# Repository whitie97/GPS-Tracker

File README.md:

# GPS-Tracker
Low Power NB-IoT GPS Tracker

Battery or USB powered.

Block Diagram:

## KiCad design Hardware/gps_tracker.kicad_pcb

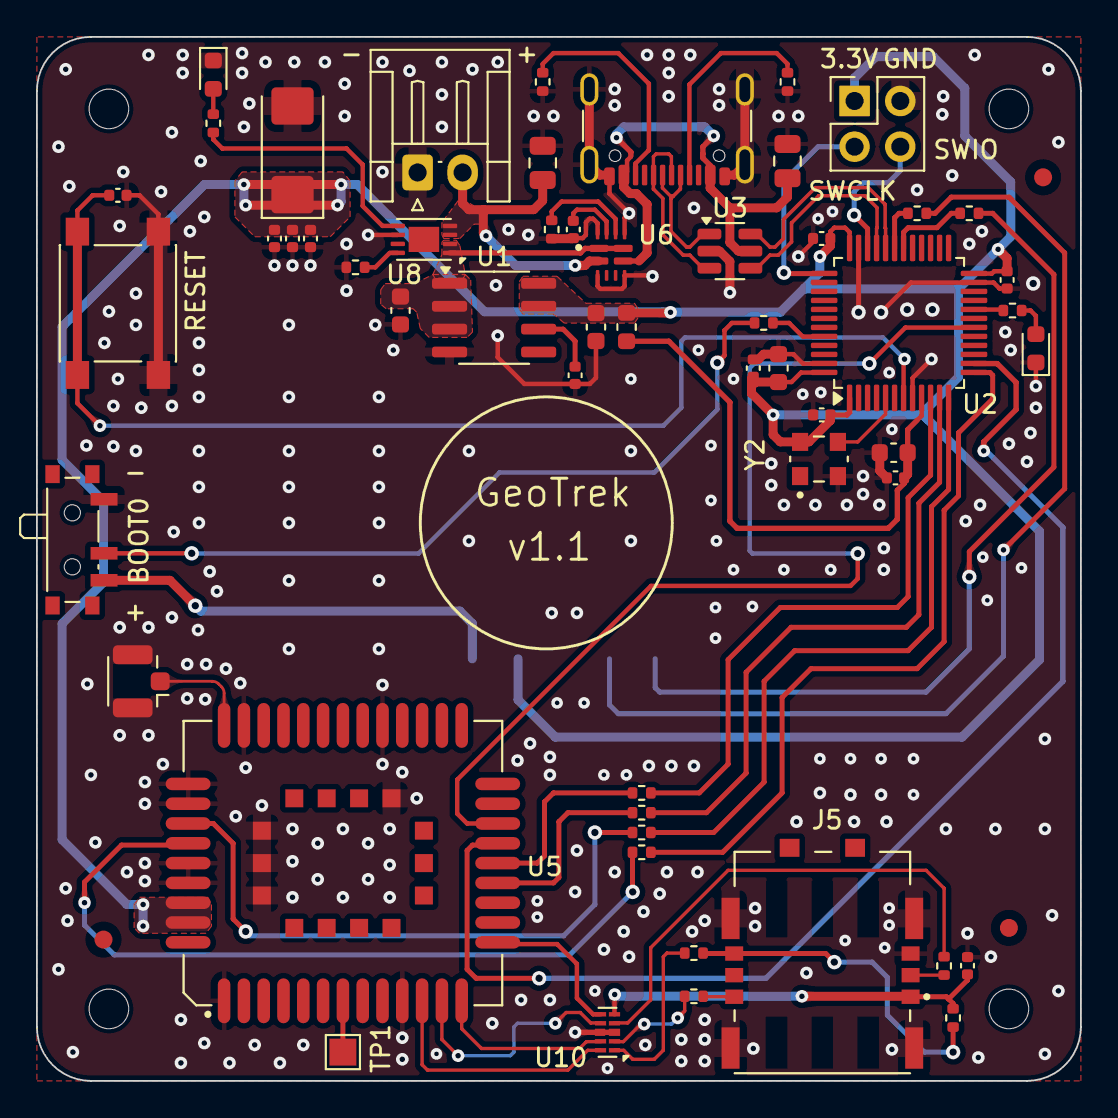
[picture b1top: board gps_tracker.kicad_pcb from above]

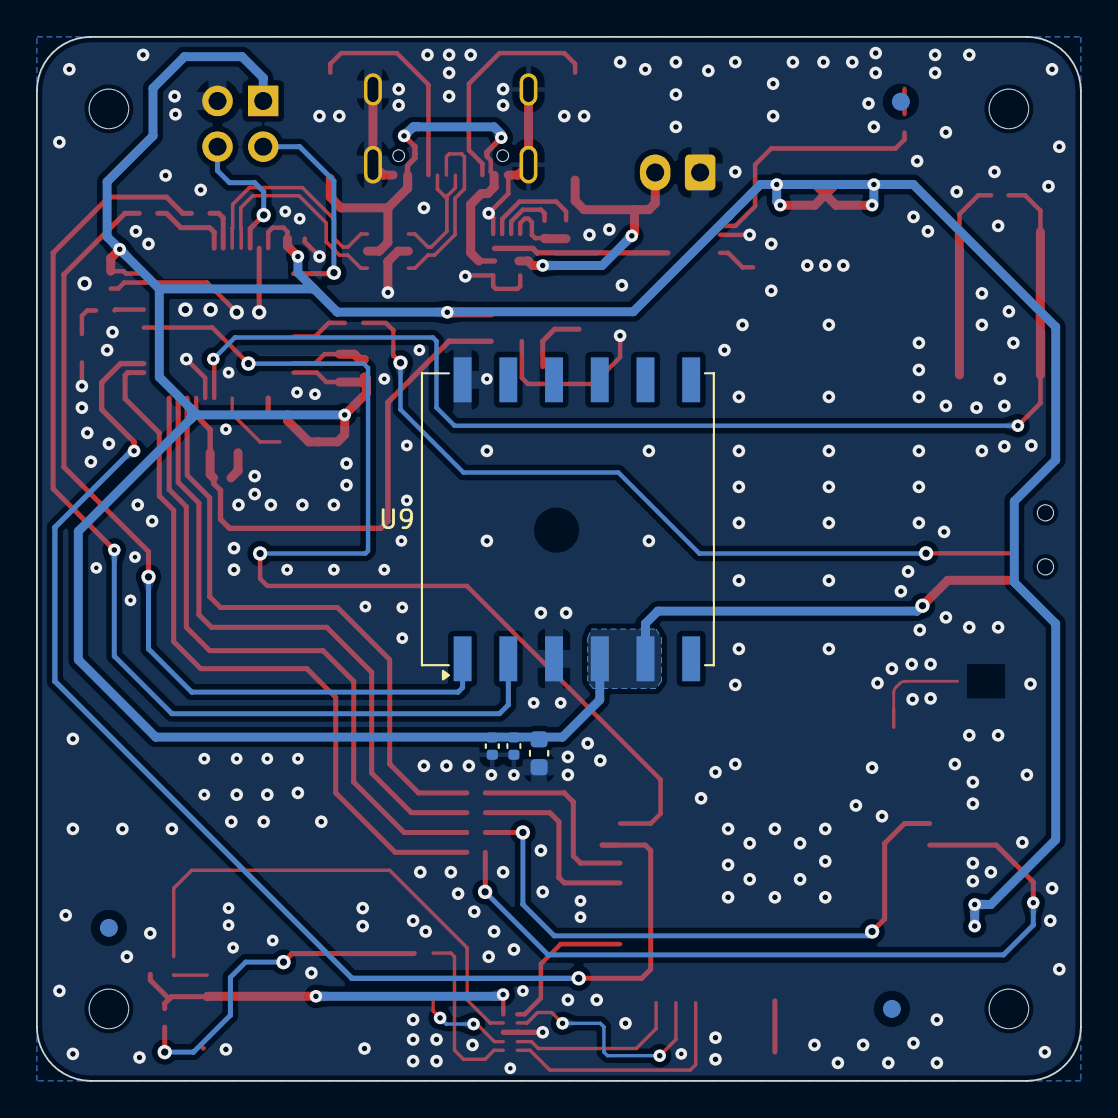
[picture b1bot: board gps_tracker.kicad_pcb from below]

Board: 4 copper layers, 58.0 x 58.0 mm, 69 parts (7 on the bottom side), 53 nets.

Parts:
C1, C2, C3, C4, C7, C8, C12, C13, C15, C21, C24, C25: 100nF; C_0402_1005Metric
C5, C6, C9, C10: 10uF; C_0603_1608Metric
C11: 1uF; C_0603_1608Metric
C14: 100uF; CP_EIA-6032-28_Kemet-C
C16: 100pF; C_0402_1005Metric
C17: 22pF; C_0402_1005Metric
C22, C23: 4.7uF; C_0805_2012Metric
D1, D2: LED; LED_0603_1608Metric
FB1: FerriteBead_Small; L_0603_1608Metric
FM1, FM2, FM3, FM4, FM5, FM6: Fiducial; Fiducial_1mm_Mask2mm
H1, H2, H3, H4: MountingHole_Pad; MountingHole_2.2mm_M2_ISO14580
J1: Conn_Coaxial; U.FL_Hirose_U.FL-R-SMT-1_Vertical
J2: Conn_01x02_Socket; JST_EH_S2B-EH_1x02_P2.50mm_Horizontal
J3: USB_C_Receptacle_USB2.0_16P; USB_C_Receptacle_GCT_USB4105-xx-A_16P_TopMnt_Horizontal
J4: Conn_02x02_Top_Bottom; PinHeader_2x02_P2.54mm_Vertical
J5: 104224-0820; MOLEX_104224-0820
R1, R2: 5.1K; R_0402_1005Metric
R3, R17: 10K; R_0402_1005Metric
R4, R14: 330R; R_0402_1005Metric
R5: 51.1K; R_0402_1005Metric
R6, R7, R15, R16: 1K; R_0402_1005Metric
R8, R9, R10, R11, R12: 22R; R_0402_1005Metric
R13: 2K; R_0402_1005Metric
SW1: SW_Push; SW_SPST_PTS645
SW2: SW_SPDT; SW_SPDT_PCM12
TP1: TestPoint; TestPoint_Pad_1.5x1.5mm
U1: MCP1727-3302xSN; SOIC-8_3.9x4.9mm_P1.27mm
U2: STM32L552CCTx; LQFP-48_7x7mm_P0.5mm
U3: USBLC6-2SC6; SOT-23-6
U5: BC660KGLAA-I03-SNASA; XCVR_BC660KGLAA-I03-SNASA
U6: TPS2121RUXR; IC_TPS2121RUXR
U8: MCP73831-2-MC; DFN-8-1EP_3x2mm_P0.5mm_EP1.7x1.4mm
U9: L80-R; Quectel_L80-R
U10: ESD224DQA; Diodes_UDFN-10_1.0x2.5mm_P0.5mm
Y2: ASEMB-24.000MHZ-LC-T; XTAL_ASEMB-24.000MHZ-LC-T

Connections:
+3.3V: C1.1, C2.1, C3.1, C4.1, C5.1, C6.1, C10.1, C14.1, C15.1, C16.1, C17.1, C24.1, C25.1, FB1.1, J4.1, SW2.3 (C), U1.7 (Sense), U1.8 (Vout), U2.1 (VBAT), U2.24 (VDD), U2.36 (VDD), U2.48 (VDD), U5.42 (VBAT), U5.43 (VBAT), U9.4 (VCC), U9.5 (V_BCKP), Y2.4 (VDD)
/CLK: R10.2, U10.2
/DATA: R8.2, U10.1
/ILIM: R5.1, U6.10 (ILIM)
/RST: R9.2, U10.4
/SS: C8.1, U6.11 (SS)
/SWD_CLK: J4.3, U2.37 (PA14)
/SWD_IO: J4.4, U2.34 (PA13)
/VCC: C21.1, J5.S1 (VCC), R17.1, U10.5
DBG_RXD_BC66: R15.1, U2.12 (PA2)
DBG_TXD_BC66: R16.1, U2.13 (PA3)
DN+: J3.A6 (D+), J3.B6 (D+), U3.3 (I/O2)
DN-: J3.A7 (D-), J3.B7 (D-), U3.1 (I/O1)
GND: C1.2, C2.2, C3.2, C4.2, C5.2, C6.2, C7.1, C8.2, C9.2, C10.2, C11.2, C12.2, C13.2, C14.2, C15.2, C16.2, C17.2, C21.2, C22.2, C23.2, C24.2, C25.2, D1.1 (K), D2.1 (K), J1.2 (Ext), J2.1, J3.A1 (GND), J3.A12 (GND), J3.S1 (SHIELD), J4.2, J5.G1 (SHD1), J5.G2 (SHD2), J5.G3 (SHD3), J5.G4 (SHD4), J5.S4 (GND), R1.2, R2.2, R5.2, R13.2, SW1.1, SW2.1 (A), U1.4 (GND), U2.8 (VSSA), U2.23 (VSS), U2.35 (VSS), U2.47 (VSS), U3.2 (GND), U5.1 (GND), U5.10 (USIM_GND), U5.27 (GND), U5.34 (GND), U5.36 (GND), U5.37 (GND), U5.40 (GND), U5.41 (GND), U5.52 (VIO_SEL), U5.56 (GND), U5.57 (GND), U5.58 (GND), U6.3 (CP2), U6.6 (PR1), U6.9 (ST), U6.12 (GND), U8.6 (V_{SS}), U9.3 (GND), U9.12 (GND), U10.3 (VSS), U10.8 (VSS), Y2.2 (GND)
HSE_IN: U2.5 (PH0), Y2.3 (OUTPUT)
unnamed: D1.2 (A), R14.2
unnamed: D2.2 (A), R4.2
unnamed: J3.A5 (CC1), R2.1
unnamed: J3.B5 (CC2), R1.1
unnamed: J5.S3 (CLK), R10.1
unnamed: J5.S6 (I/O), R8.1, R17.2
unnamed: J5.S2 (RST), R9.1
unnamed: R3.2, SW2.2 (B)
unnamed: C13.1, U1.6 (Cdelay)
unnamed: R4.1, U2.20 (PB2)
unnamed: R3.1, U2.44 (PH3)
unnamed: TP1.1, U5.7 (BOOT)
unnamed: R15.2, U5.38 (DBG_RXD)
unnamed: R16.2, U5.39 (DBG_TXD)
unnamed: R6.2, U5.18 (MAIN_RXD)
unnamed: R7.2, U5.17 (MAIN_TXD)
unnamed: R13.1, U8.8 (PROG)
unnamed: R14.1, U8.5 (STAT)
unnamed: R12.1, U9.1 (RXD1)
unnamed: R11.1, U9.2 (TXD1)
PSM_EINT_MCU: U2.14 (PA4), U5.19 (PSM_EINT)
RF_ANT: J1.1 (In), U5.35 (ANT_RF)
RI_BC66: U2.18 (PB0), U5.20 (RI)
RXD_BC66: R6.1, U2.10 (PA0)
RX_GPS: R12.2, U2.30 (PA9)
SIM_CLK: U5.13 (USIM_CLK), U10.9
SIM_DATA: U5.11 (USIM_DATA), U10.10
SIM_RST: U5.12 (USIM_RST), U10.7
SIM_VDD: U5.14 (USIM_VDD), U10.6
SW_NRST: C7.2, SW1.2, U2.7 (NRST)
TXD_BC66: R7.1, U2.11 (PA1)
TX_GPS: R11.2, U2.31 (PA10)
USB_+: U2.33 (PA12), U3.4 (I/O2)
USB_-: U2.32 (PA11), U3.6 (I/O1)
VBAT: C23.1, J2.2, U6.2 (IN2), U8.3 (V_{BAT}), U8.4 (V_{BAT})
VBUS: C22.1, J3.A4 (VBUS), J3.A9 (VBUS), J3.B4 (VBUS), J3.B9 (VBUS), U3.5 (VBUS), U6.7 (IN1)
VDDA_PWR: C11.1, C12.1, FB1.2, U2.9 (VDDA)
VOUT: C9.1, U1.1 (Vin), U1.2 (Vin), U1.3 (~SHDN), U6.1 (OUT), U6.8 (OUT), U8.1 (V_{DD}), U8.2 (V_{DD})

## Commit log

2024-09-17 Create Hardware
2024-09-17 Create tmp
